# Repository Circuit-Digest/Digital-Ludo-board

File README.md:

# [Digital-Ludo-board](https://circuitdigest.com/microcontroller-projects/build-a-smart-digital-game-board-using-multicolour-pcb)

## Gallery

<table align="center">
  <tr>
    <td align="center">
      
    </td>
    <td align="center">
      
    </td>
  </tr>
  <tr>
    <td align="center">
      
    </td>
    <td align="center">
      
    </td>
  </tr>
</table>

---
Ludo, one of our cherished childhood board games, holds a special place in our hearts. Its simple yet engaging gameplay has provided countless hours of fun and bonding. However, as times have changed, so have our ways of enjoying these nostalgic pastimes. Today, children often experience classic games like Ludo through smartphones and gaming consoles, losing the physical gameplay and interpersonal connection of traditional board games.

What if we could bridge the gap between the old and the new by creating a digital version of the Ludo board? So let's create a Digital Ludo Board, a modern take on this classic game that combines the nostalgia of the physical game with the convenience and interactivity of the digital world. Designed and built from scratch, this is not only a fun project but also an opportunity to try out the new multicolor PCB.

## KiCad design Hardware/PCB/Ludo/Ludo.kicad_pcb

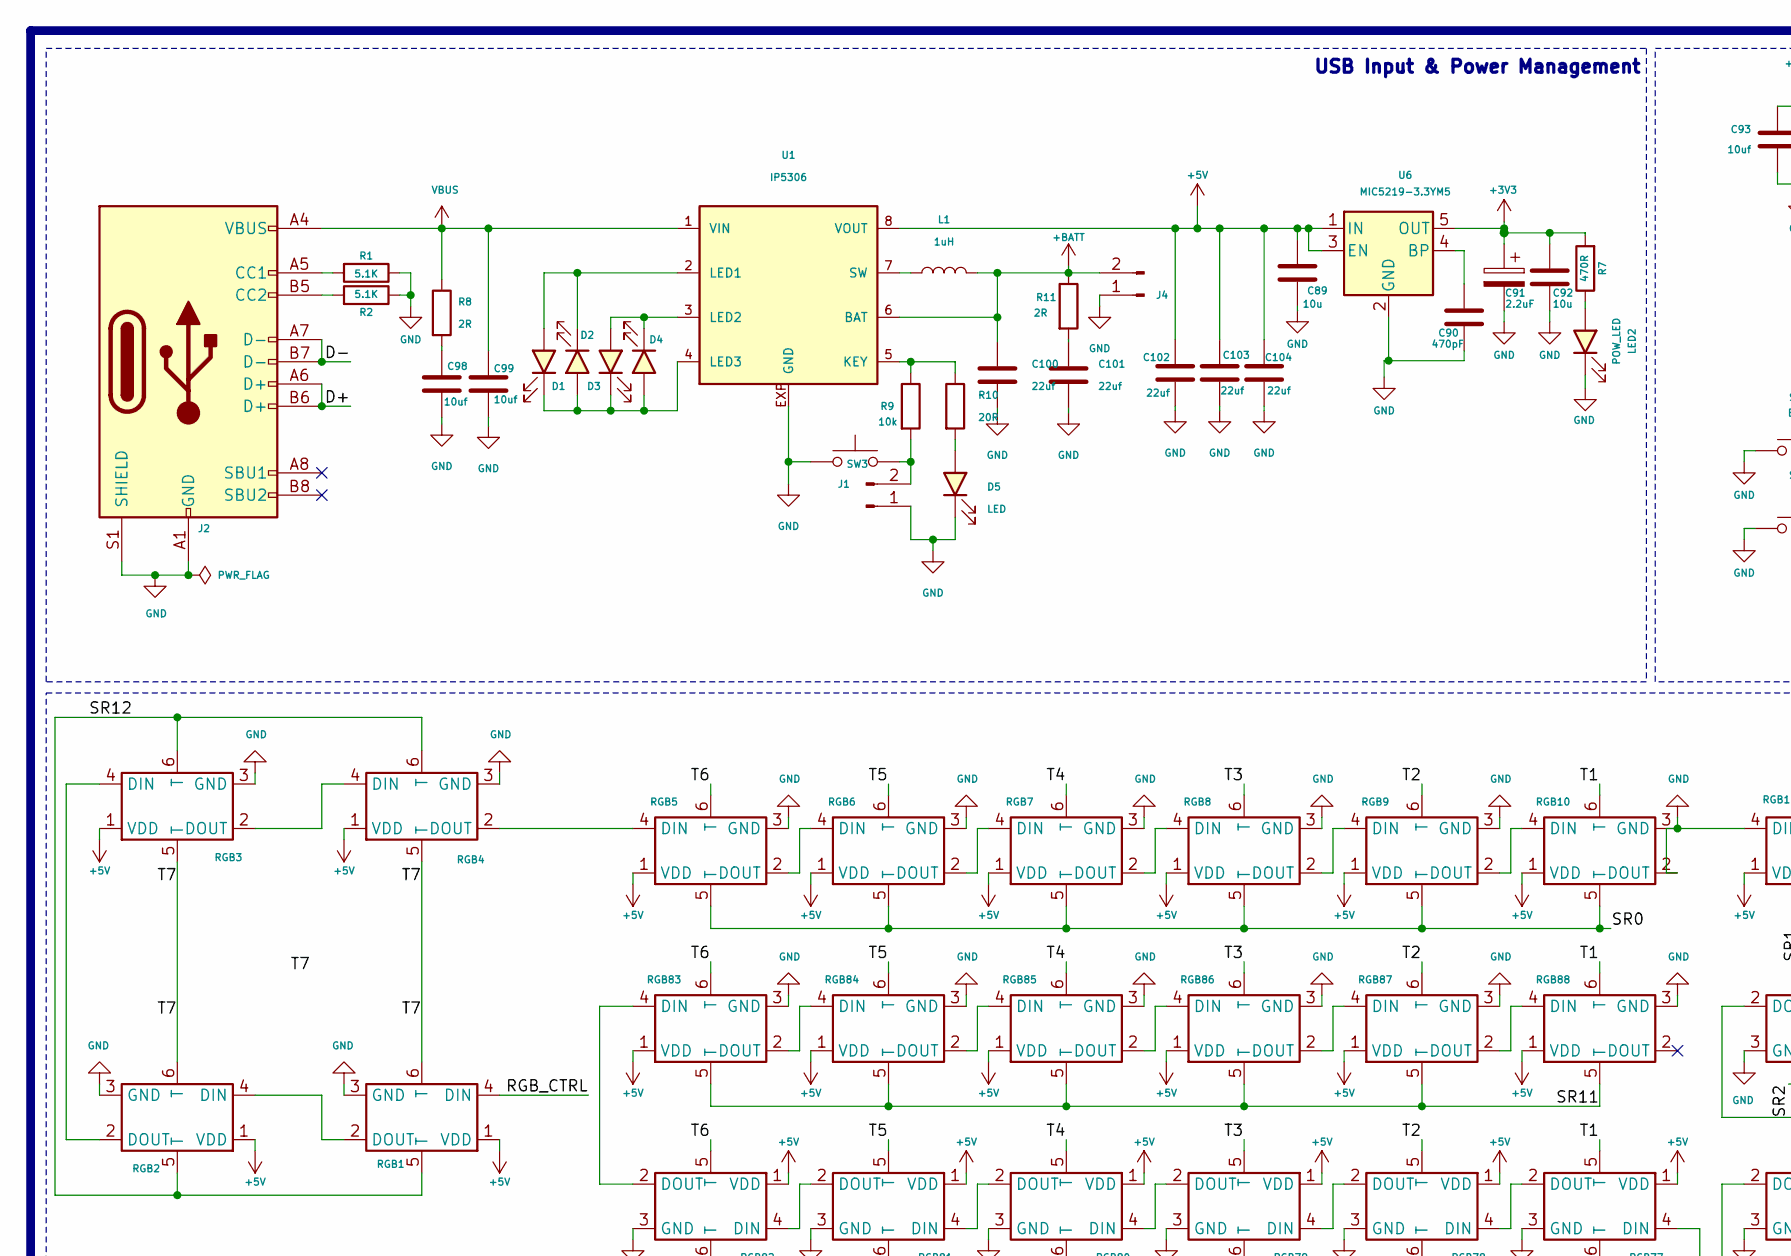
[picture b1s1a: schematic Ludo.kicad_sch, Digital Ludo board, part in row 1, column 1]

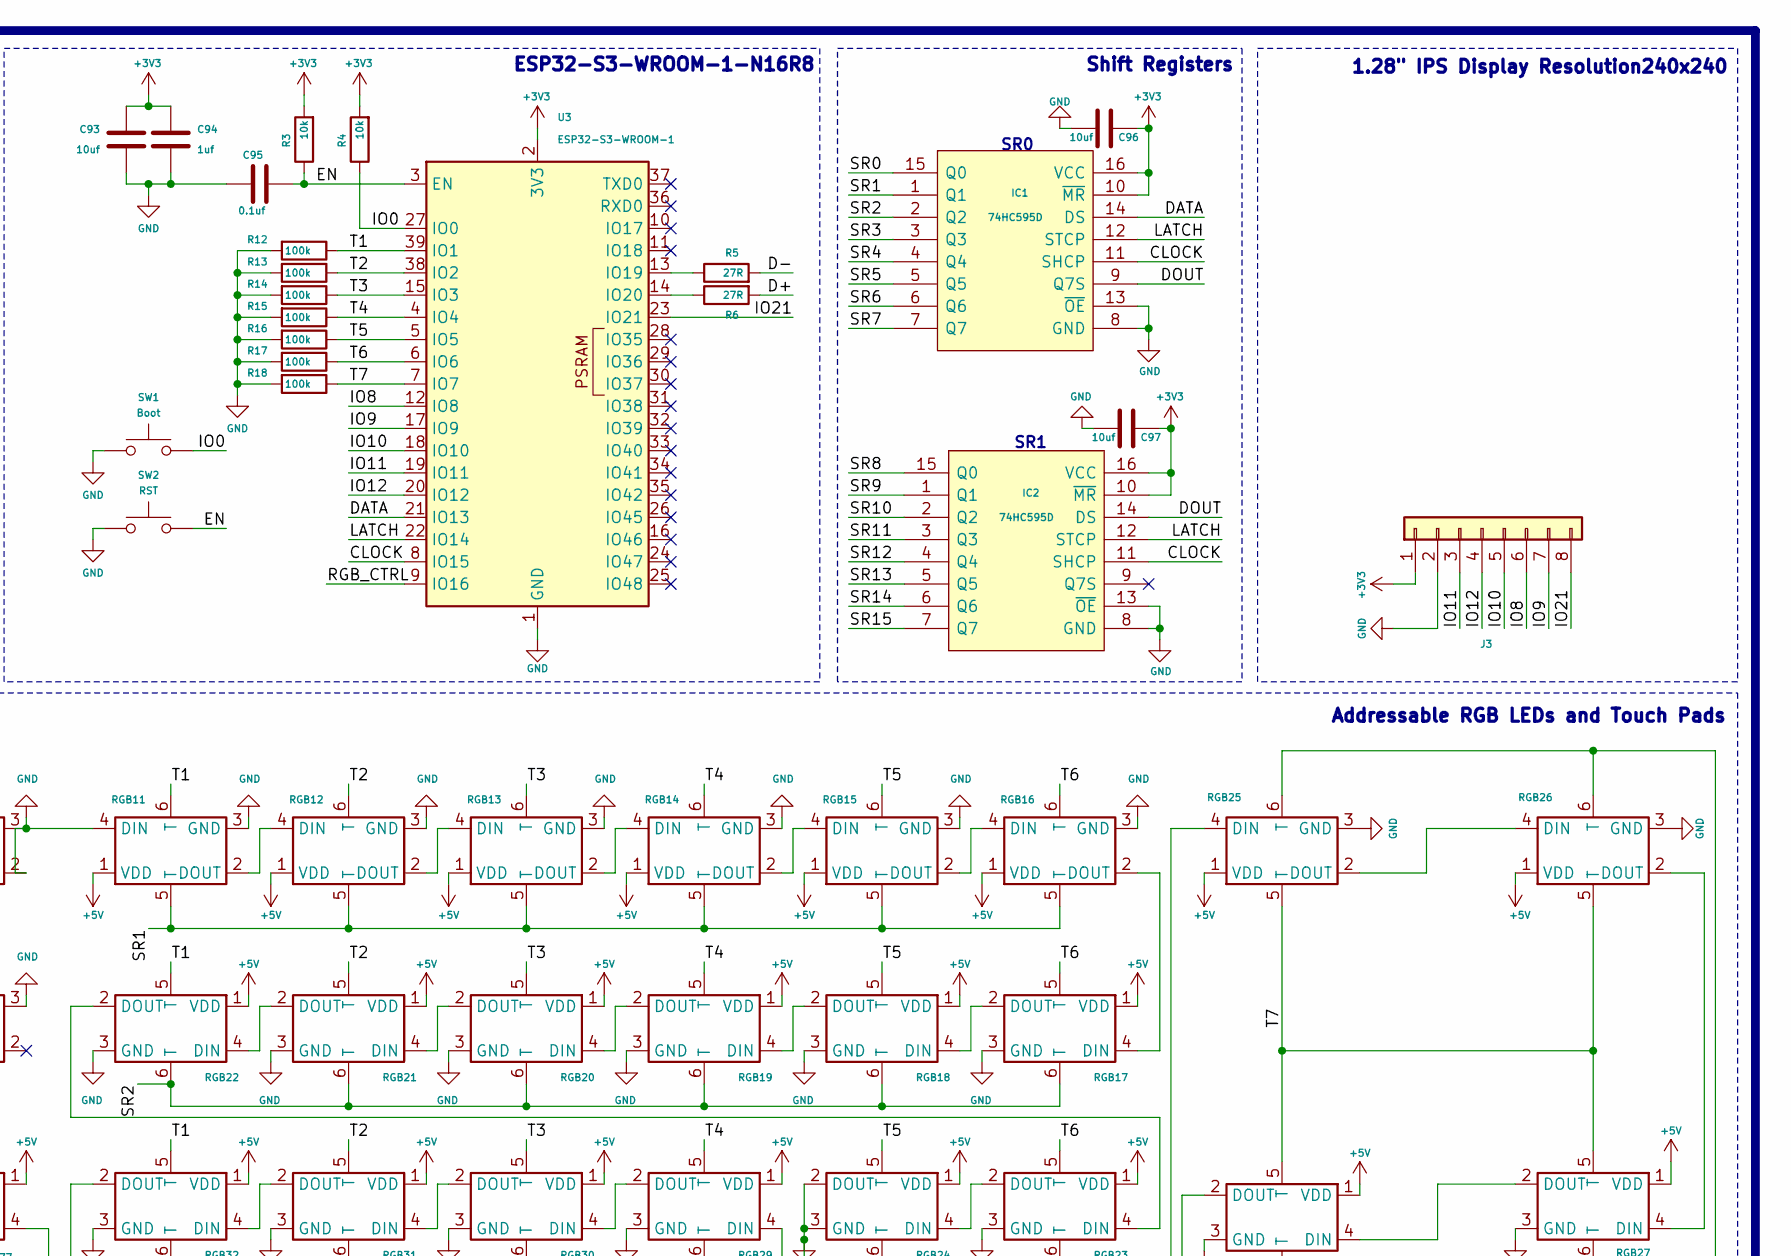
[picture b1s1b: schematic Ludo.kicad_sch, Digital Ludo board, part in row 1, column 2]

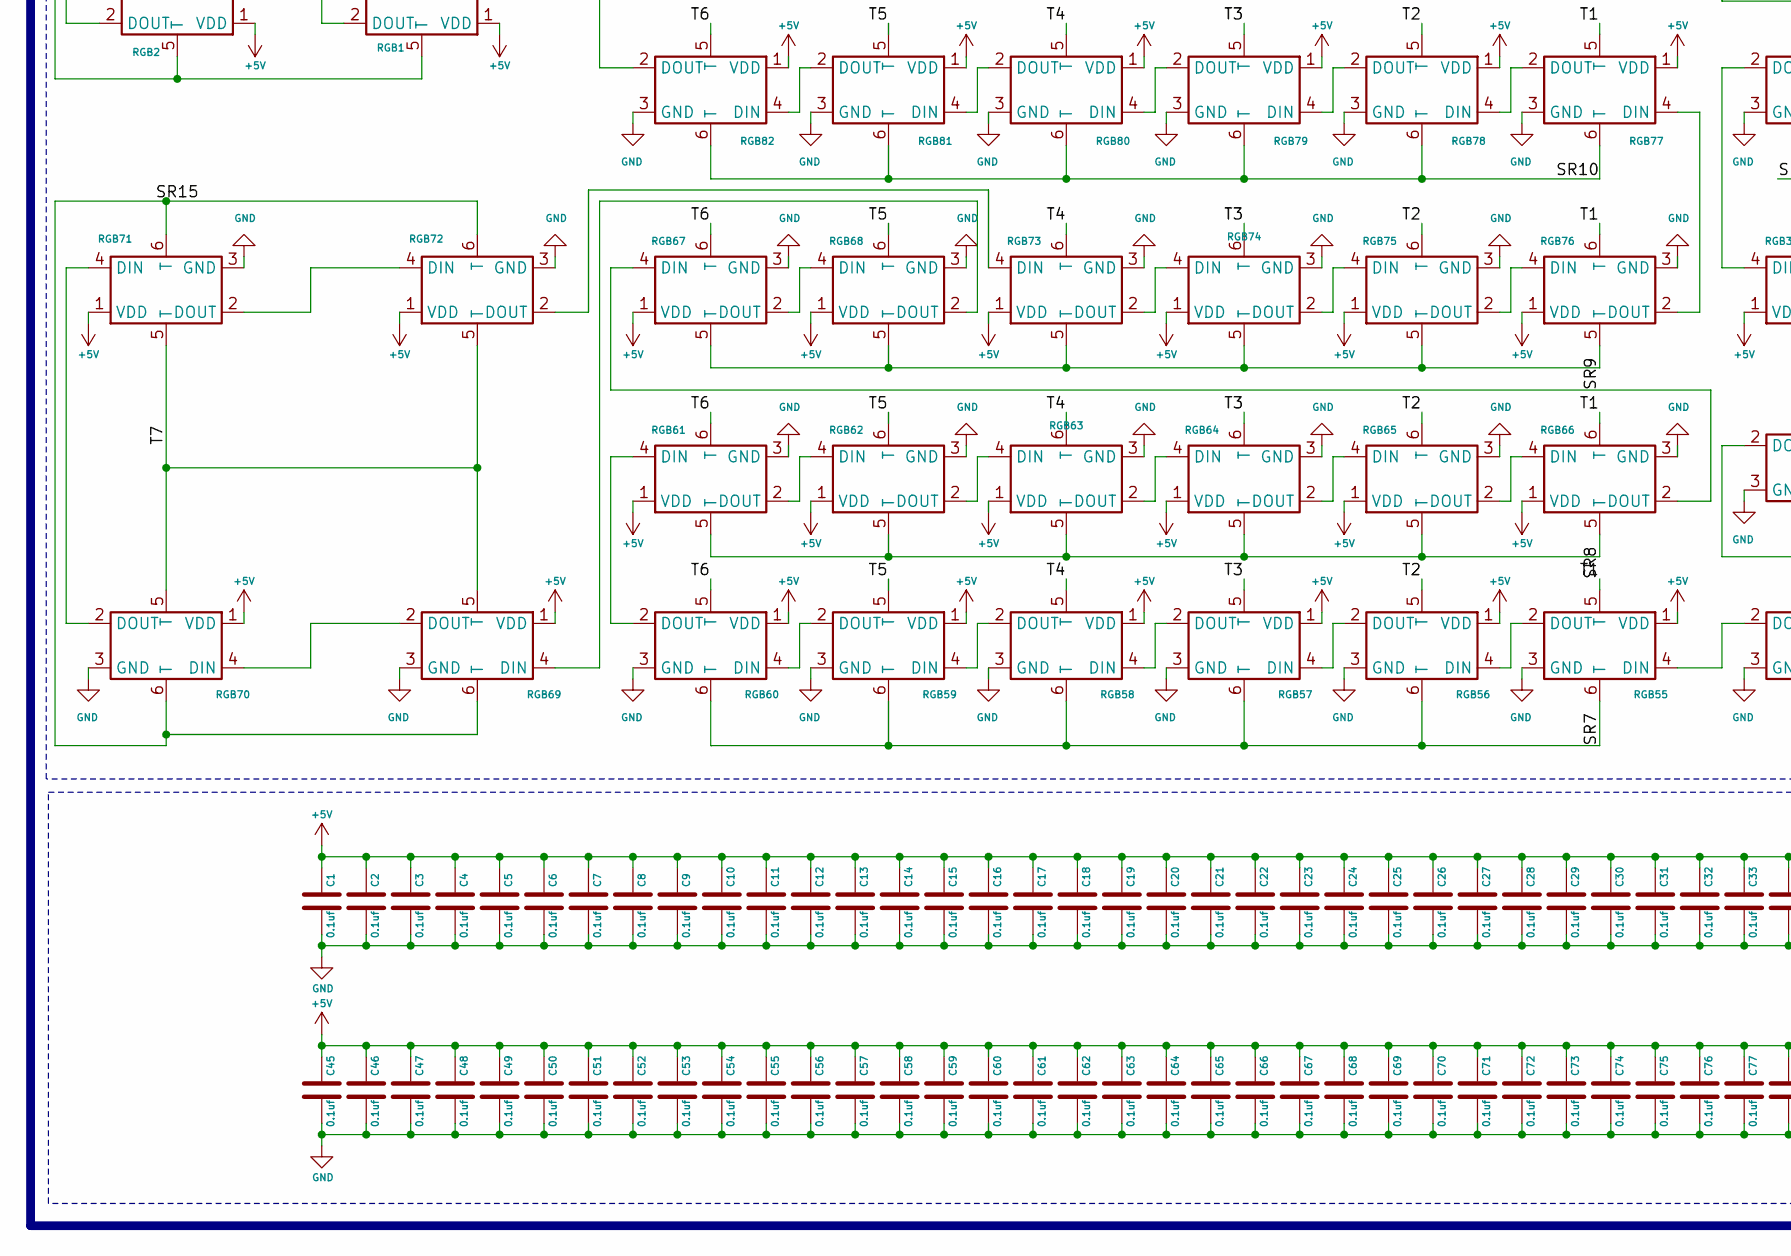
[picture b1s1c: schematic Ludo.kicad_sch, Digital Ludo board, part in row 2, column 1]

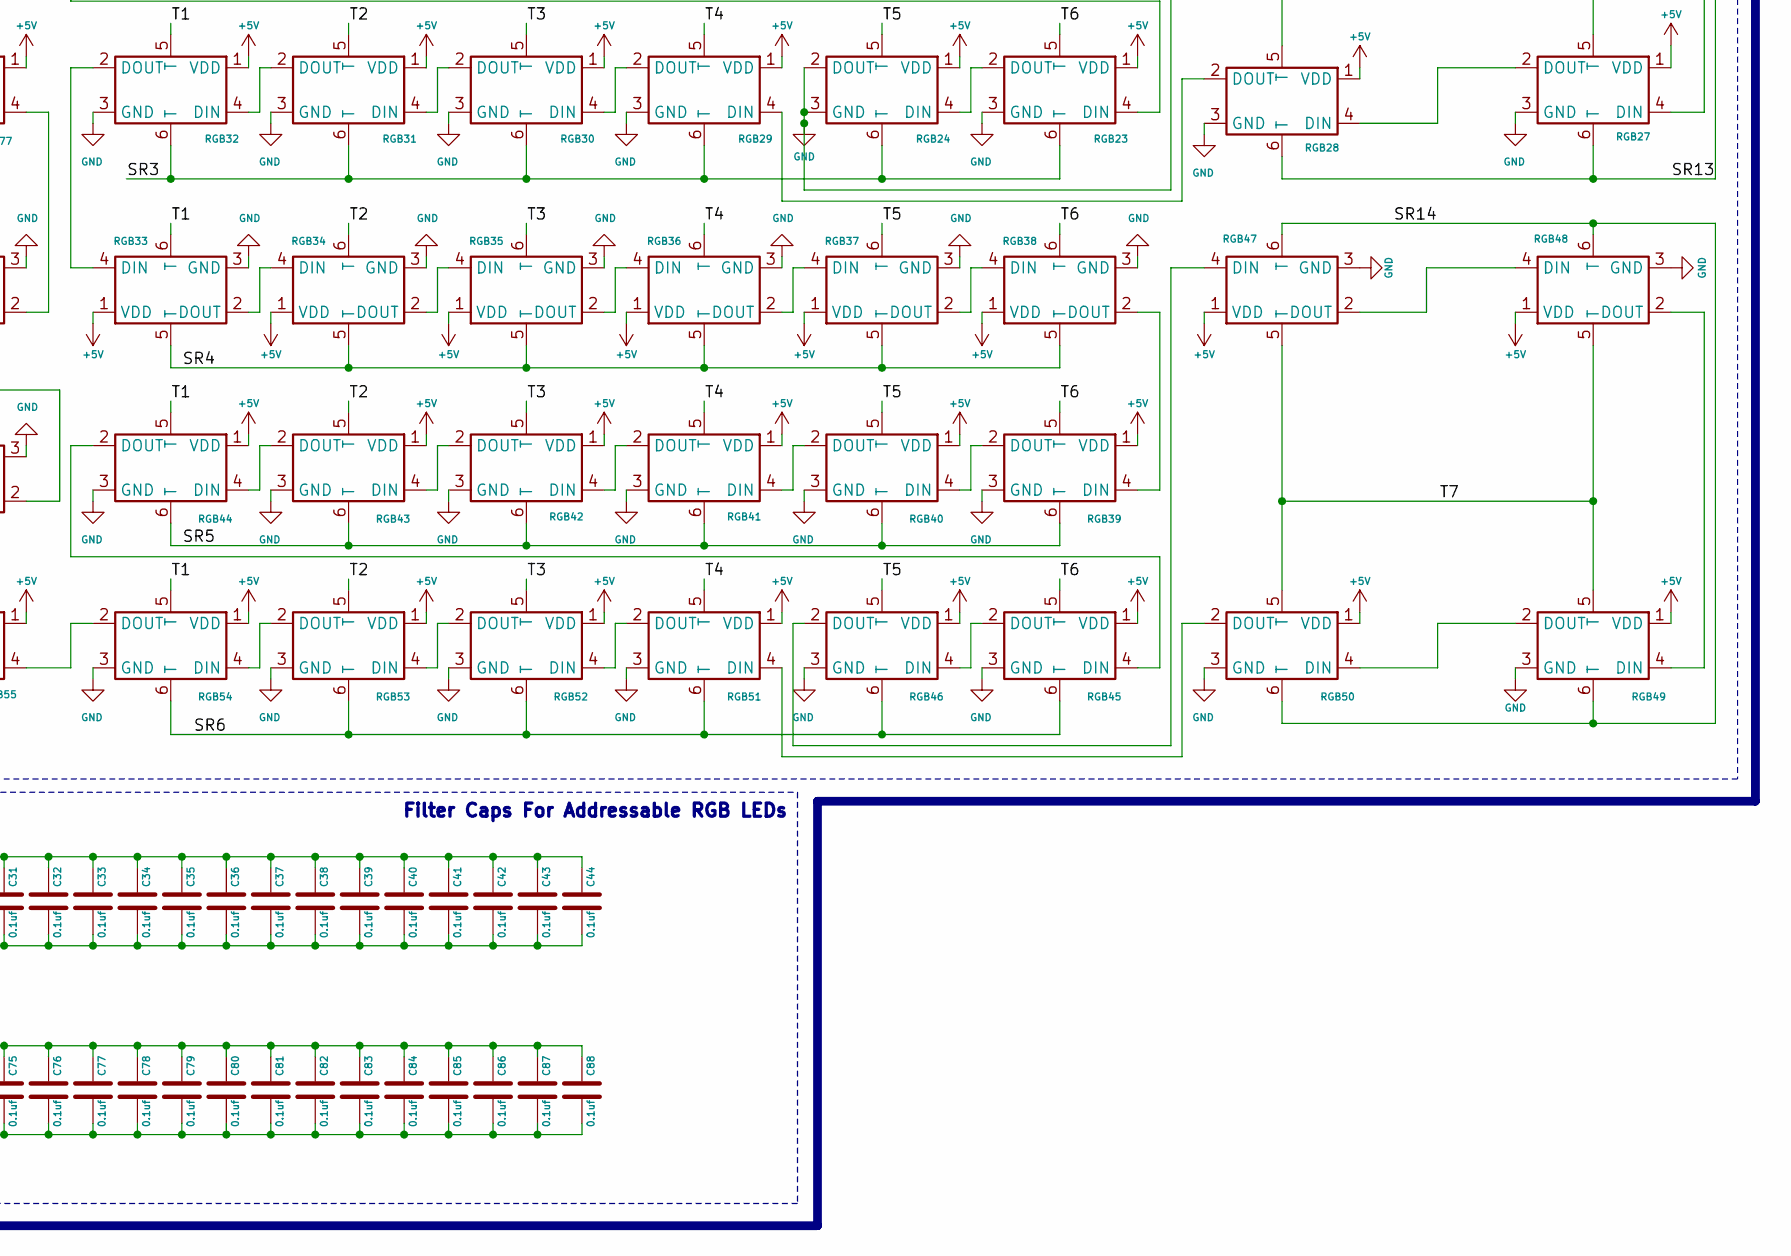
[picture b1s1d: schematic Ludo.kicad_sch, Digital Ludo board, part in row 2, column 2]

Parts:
C1, C2, C3, C4, C5, C6, C7, C8, C9, C10, C11, C12, C13, C14, C15, C16, C17, C18, C19, C20, C21, C22, C23, C24, C25, C26, C27, C28, C29, C30, C31, C32, C33, C34, C35, C36, C37, C38, C39, C40, C41, C42, C43, C44, C45, C46, C47, C48, C49, C50, C51, C52, C53, C54, C55, C56, C57, C58, C59, C60, C61, C62, C63, C64, C65, C66, C67, C68, C69, C70, C71, C72, C73, C74, C75, C76, C77, C78, C79, C80, C81, C82, C83, C84, C85, C86, C87, C88, C95: 0.1uf; C_0603_1608Metric
C89, C92: 10u; C_0603_1608Metric
C90: 470pF; C_0603_1608Metric
C91: 2.2uF; C_0805_2012Metric
C93, C96, C97, C98, C99: 10uf; C_0603_1608Metric
C94: 1uf; C_0603_1608Metric
C100, C101, C102, C103, C104: 22uf; C_0603_1608Metric
D1, D2, D3, D4, D5: LED; LED_0603_1608Metric
IC1, IC2: 74HC595D; 74HC595DQ100118; Mouser Part Number 771-74HC595D-Q100
J1, J4: Conn_01x02_Male; JST_PH_S2B-PH-SM4-TB_1x02-1MP_P2.00mm_Horizontal
J2: USB_C_Receptacle_USB2.0; USB_C_Receptacle_HRO_TYPE-C-31-M-12
J3: Conn_01x08; JST_PH_S8B-PH-SM4-TB_1x08-1MP_P2.00mm_Horizontal
L1: 1uH; IND1uh
LED2: POW_LED; LED_0603_1608Metric
R1, R2: 5.1K; R_0603_1608Metric
R3, R4, R9: 10k; R_0603_1608Metric
R5, R6: 27R; R_0603_1608Metric
R7: 470R; R_0603_1608Metric
R8, R11: 2R; R_0603_1608Metric
R10: 20R; R_0603_1608Metric
R12, R13, R14, R15, R16, R17, R18: 100k; R_0603_1608Metric
RGB1, RGB2, RGB3, RGB4, RGB5, RGB6, RGB7, RGB8, RGB9, RGB10, RGB11, RGB12, RGB13, RGB14, RGB15, RGB16, RGB17, RGB18, RGB19, RGB20, RGB21, RGB22, RGB23, RGB24, RGB25, RGB26, RGB27, RGB28, RGB29, RGB30, RGB31, RGB32, RGB33, RGB34, RGB35, RGB36, RGB37, RGB38, RGB39, RGB40, RGB41, RGB42, RGB43, RGB44, RGB45, RGB46, RGB47, RGB48, RGB49, RGB50, RGB51, RGB52, RGB53, RGB54, RGB55, RGB56, RGB57, RGB58, RGB59, RGB60, RGB61, RGB62, RGB63, RGB64, RGB65, RGB66, RGB67, RGB68, RGB69, RGB70, RGB71, RGB72, RGB73, RGB74, RGB75, RGB76, RGB77, RGB78, RGB79, RGB80, RGB81, RGB82, RGB83, RGB84, RGB85, RGB86, RGB87, RGB88: SK6812MINI-E_C5149201; SK6812MINI-E_1
SW1: Boot; Tactile 3x4x2mm TS-A010
SW2: RST; Tactile 3x4x2mm TS-A010
SW3: Boot; SW-SMD_TS24CA
U1: IP5306; IP5306-SOP8
U3: ESP32-S3-WROOM-1
U6: MIC5219-3.3YM5; SOT-23-5

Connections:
+3V3: C91.1, C92.1, C93.1, C94.1, C96.1, C97.1, IC1.10 (~MR), IC1.16 (VCC), IC2.10 (~MR), IC2.16 (VCC), J3.1, R3.2, R4.2, R7.2, U3.2 (3V3), U6.5 (OUT)
+5V: C1.1, C2.1, C3.1, C4.1, C5.1, C6.1, C7.1, C8.1, C9.1, C10.1, C11.1, C12.1, C13.1, C14.1, C15.1, C16.1, C17.1, C18.1, C19.1, C20.1, C21.1, C22.1, C23.1, C24.1, C25.1, C26.1, C27.1, C28.1, C29.1, C30.1, C31.1, C32.1, C33.1, C34.1, C35.1, C36.1, C37.1, C38.1, C39.1, C40.1, C41.1, C42.1, C43.1, C44.1, C45.1, C46.1, C47.1, C48.1, C49.1, C50.1, C51.1, C52.1, C53.1, C54.1, C55.1, C56.1, C57.1, C58.1, C59.1, C60.1, C61.1, C62.1, C63.1, C64.1, C65.1, C66.1, C67.1, C68.1, C69.1, C70.1, C71.1, C72.1, C73.1, C74.1, C75.1, C76.1, C77.1, C78.1, C79.1, C80.1, C81.1, C82.1, C83.1, C84.1, C85.1, C86.1, C87.1, C88.1, C89.1, C102.1, C103.1, C104.1, RGB1.1 (VDD), RGB2.1 (VDD), RGB3.1 (VDD), RGB4.1 (VDD), RGB5.1 (VDD), RGB6.1 (VDD), RGB7.1 (VDD), RGB8.1 (VDD), RGB9.1 (VDD), RGB10.1 (VDD), RGB11.1 (VDD), RGB12.1 (VDD), RGB13.1 (VDD), RGB14.1 (VDD), RGB15.1 (VDD), RGB16.1 (VDD), RGB17.1 (VDD), RGB18.1 (VDD), RGB19.1 (VDD), RGB20.1 (VDD), RGB21.1 (VDD), RGB22.1 (VDD), RGB23.1 (VDD), RGB24.1 (VDD), RGB25.1 (VDD), RGB26.1 (VDD), RGB27.1 (VDD), RGB28.1 (VDD), RGB29.1 (VDD), RGB30.1 (VDD), RGB31.1 (VDD), RGB32.1 (VDD), RGB33.1 (VDD), RGB34.1 (VDD), RGB35.1 (VDD), RGB36.1 (VDD), RGB37.1 (VDD), RGB38.1 (VDD), RGB39.1 (VDD), RGB40.1 (VDD), RGB41.1 (VDD), RGB42.1 (VDD), RGB43.1 (VDD), RGB44.1 (VDD), RGB45.1 (VDD), RGB46.1 (VDD), RGB47.1 (VDD), RGB48.1 (VDD), RGB49.1 (VDD), RGB50.1 (VDD), RGB51.1 (VDD), RGB52.1 (VDD), RGB53.1 (VDD), RGB54.1 (VDD), RGB55.1 (VDD), RGB56.1 (VDD), RGB57.1 (VDD), RGB58.1 (VDD), RGB59.1 (VDD), RGB60.1 (VDD), RGB61.1 (VDD), RGB62.1 (VDD), RGB63.1 (VDD), RGB64.1 (VDD), RGB65.1 (VDD), RGB66.1 (VDD), RGB67.1 (VDD), RGB68.1 (VDD), RGB69.1 (VDD), RGB70.1 (VDD), RGB71.1 (VDD), RGB72.1 (VDD), RGB73.1 (VDD), RGB74.1 (VDD), RGB75.1 (VDD), RGB76.1 (VDD), RGB77.1 (VDD), RGB78.1 (VDD), RGB79.1 (VDD), RGB80.1 (VDD), RGB81.1 (VDD), RGB82.1 (VDD), RGB83.1 (VDD), RGB84.1 (VDD), RGB85.1 (VDD), RGB86.1 (VDD), RGB87.1 (VDD), RGB88.1 (VDD), U1.8 (VOUT), U6.1 (IN), U6.3 (EN)
+BATT: C100.1, J4.2, L1.2, R11.1, U1.6 (BAT)
/CLOCK: IC1.11 (SHCP), IC2.11 (SHCP), U3.8 (IO15)
/D+: J2.A6 (D+), J2.B6 (D+), R6.2
/D-: J2.A7 (D-), J2.B7 (D-), R5.2
/DATA: IC1.14 (DS), U3.21 (IO13)
/DOUT: IC1.9 (Q7S), IC2.14 (DS)
/EN: C95.1, R3.1, SW2.2, U3.3 (EN)
/IO0: R4.1, SW1.2, U3.27 (IO0)
/IO8: J3.6, U3.12 (IO8)
/IO9: J3.7, U3.17 (IO9)
/IO10: J3.5, U3.18 (IO10)
/IO11: J3.3, U3.19 (IO11)
/IO12: J3.4, U3.20 (IO12)
/IO21: J3.8, U3.23 (IO21)
/LATCH: IC1.12 (STCP), IC2.12 (STCP), U3.22 (IO14)
/RGB_CTRL: RGB1.4 (DIN), U3.9 (IO16)
/SR0: IC1.15 (Q0), RGB5.5 (T), RGB6.5 (T), RGB7.5 (T), RGB8.5 (T), RGB9.5 (T), RGB10.5 (T)
/SR1: IC1.1 (Q1), RGB11.5 (T), RGB12.5 (T), RGB13.5 (T), RGB14.5 (T), RGB15.5 (T), RGB16.5 (T)
/SR2: IC1.2 (Q2), RGB17.6 (T), RGB18.6 (T), RGB19.6 (T), RGB20.6 (T), RGB21.6 (T), RGB22.6 (T)
/SR3: IC1.3 (Q3), RGB23.6 (T), RGB24.6 (T), RGB29.6 (T), RGB30.6 (T), RGB31.6 (T), RGB32.6 (T)
/SR4: IC1.4 (Q4), RGB33.5 (T), RGB34.5 (T), RGB35.5 (T), RGB36.5 (T), RGB37.5 (T), RGB38.5 (T)
/SR5: IC1.5 (Q5), RGB39.6 (T), RGB40.6 (T), RGB41.6 (T), RGB42.6 (T), RGB43.6 (T), RGB44.6 (T)
/SR6: IC1.6 (Q6), RGB45.6 (T), RGB46.6 (T), RGB51.6 (T), RGB52.6 (T), RGB53.6 (T), RGB54.6 (T)
/SR7: IC1.7 (Q7), RGB55.6 (T), RGB56.6 (T), RGB57.6 (T), RGB58.6 (T), RGB59.6 (T), RGB60.6 (T)
/SR8: IC2.15 (Q0), RGB61.5 (T), RGB62.5 (T), RGB63.5 (T), RGB64.5 (T), RGB65.5 (T), RGB66.5 (T)
/SR9: IC2.1 (Q1), RGB67.5 (T), RGB68.5 (T), RGB73.5 (T), RGB74.5 (T), RGB75.5 (T), RGB76.5 (T)
/SR10: IC2.2 (Q2), RGB77.6 (T), RGB78.6 (T), RGB79.6 (T), RGB80.6 (T), RGB81.6 (T), RGB82.6 (T)
/SR11: IC2.3 (Q3), RGB83.5 (T), RGB84.5 (T), RGB85.5 (T), RGB86.5 (T), RGB87.5 (T), RGB88.5 (T)
/SR12: IC2.4 (Q4), RGB1.5 (T), RGB2.5 (T), RGB3.6 (T), RGB4.6 (T)
/SR13: IC2.5 (Q5), RGB25.6 (T), RGB26.6 (T), RGB27.6 (T), RGB28.6 (T)
/SR14: IC2.6 (Q6), RGB47.6 (T), RGB48.6 (T), RGB49.6 (T), RGB50.6 (T)
/SR15: IC2.7 (Q7), RGB69.6 (T), RGB70.6 (T), RGB71.6 (T), RGB72.6 (T)
/T1: R12.1, RGB10.6 (T), RGB11.6 (T), RGB22.5 (T), RGB32.5 (T), RGB33.6 (T), RGB44.5 (T), RGB54.5 (T), RGB55.5 (T), RGB66.6 (T), RGB76.6 (T), RGB77.5 (T), RGB88.6 (T), U3.39 (IO1)
/T2: R13.1, RGB9.6 (T), RGB12.6 (T), RGB21.5 (T), RGB31.5 (T), RGB34.6 (T), RGB43.5 (T), RGB53.5 (T), RGB56.5 (T), RGB65.6 (T), RGB75.6 (T), RGB78.5 (T), RGB87.6 (T), U3.38 (IO2)
/T3: R14.1, RGB8.6 (T), RGB13.6 (T), RGB20.5 (T), RGB30.5 (T), RGB35.6 (T), RGB42.5 (T), RGB52.5 (T), RGB57.5 (T), RGB64.6 (T), RGB74.6 (T), RGB79.5 (T), RGB86.6 (T), U3.15 (IO3)
/T4: R15.1, RGB7.6 (T), RGB14.6 (T), RGB19.5 (T), RGB29.5 (T), RGB36.6 (T), RGB41.5 (T), RGB51.5 (T), RGB58.5 (T), RGB63.6 (T), RGB73.6 (T), RGB80.5 (T), RGB85.6 (T), U3.4 (IO4)
/T5: R16.1, RGB6.6 (T), RGB15.6 (T), RGB18.5 (T), RGB24.5 (T), RGB37.6 (T), RGB40.5 (T), RGB46.5 (T), RGB59.5 (T), RGB62.6 (T), RGB68.6 (T), RGB81.5 (T), RGB84.6 (T), U3.5 (IO5)
/T6: R17.1, RGB5.6 (T), RGB16.6 (T), RGB17.5 (T), RGB23.5 (T), RGB38.6 (T), RGB39.5 (T), RGB45.5 (T), RGB60.5 (T), RGB61.6 (T), RGB67.6 (T), RGB82.5 (T), RGB83.6 (T), U3.6 (IO6)
/T7: R18.1, RGB1.6 (T), RGB2.6 (T), RGB3.5 (T), RGB4.5 (T), RGB25.5 (T), RGB26.5 (T), RGB27.5 (T), RGB28.5 (T), RGB47.5 (T), RGB48.5 (T), RGB49.5 (T), RGB50.5 (T), RGB69.5 (T), RGB70.5 (T), RGB71.5 (T), RGB72.5 (T), U3.7 (IO7)
unnamed: C98.1, R8.2
unnamed: C101.1, R11.2
unnamed: D1.2 (A), D2.1 (K), U1.2 (LED1)
unnamed: D1.1 (K), D2.2 (A), D3.1 (K), D4.2 (A), U1.4 (LED3)
unnamed: D3.2 (A), D4.1 (K), U1.3 (LED2)
unnamed: D5.2 (A), R10.2
unnamed: J1.2, R9.2, SW3.2
unnamed: J2.A5 (CC1), R1.2
unnamed: J2.B5 (CC2), R2.2
unnamed: LED2.2 (A), R7.1
unnamed: RGB1.2 (DOUT), RGB2.4 (DIN)
unnamed: RGB2.2 (DOUT), RGB3.4 (DIN)
unnamed: RGB3.2 (DOUT), RGB4.4 (DIN)
unnamed: RGB4.2 (DOUT), RGB5.4 (DIN)
unnamed: RGB5.2 (DOUT), RGB6.4 (DIN)
unnamed: RGB6.2 (DOUT), RGB7.4 (DIN)
unnamed: RGB7.2 (DOUT), RGB8.4 (DIN)
unnamed: RGB8.2 (DOUT), RGB9.4 (DIN)
unnamed: RGB9.2 (DOUT), RGB10.4 (DIN)
unnamed: RGB11.2 (DOUT), RGB12.4 (DIN)
unnamed: RGB12.2 (DOUT), RGB13.4 (DIN)
unnamed: RGB13.2 (DOUT), RGB14.4 (DIN)
unnamed: RGB14.2 (DOUT), RGB15.4 (DIN)
unnamed: RGB15.2 (DOUT), RGB16.4 (DIN)
unnamed: RGB16.2 (DOUT), RGB17.4 (DIN)
unnamed: RGB17.2 (DOUT), RGB18.4 (DIN)
unnamed: RGB18.2 (DOUT), RGB19.4 (DIN)
unnamed: RGB19.2 (DOUT), RGB20.4 (DIN)
unnamed: RGB20.2 (DOUT), RGB21.4 (DIN)
unnamed: RGB21.2 (DOUT), RGB22.4 (DIN)
unnamed: RGB22.2 (DOUT), RGB23.4 (DIN)
unnamed: RGB23.2 (DOUT), RGB24.4 (DIN)
unnamed: RGB25.2 (DOUT), RGB26.4 (DIN)
unnamed: RGB26.2 (DOUT), RGB27.4 (DIN)
unnamed: RGB27.2 (DOUT), RGB28.4 (DIN)
unnamed: RGB28.2 (DOUT), RGB29.4 (DIN)
unnamed: RGB29.2 (DOUT), RGB30.4 (DIN)
unnamed: RGB30.2 (DOUT), RGB31.4 (DIN)
unnamed: RGB31.2 (DOUT), RGB32.4 (DIN)
unnamed: RGB32.2 (DOUT), RGB33.4 (DIN)
unnamed: RGB33.2 (DOUT), RGB34.4 (DIN)
unnamed: RGB34.2 (DOUT), RGB35.4 (DIN)
unnamed: RGB35.2 (DOUT), RGB36.4 (DIN)
unnamed: RGB36.2 (DOUT), RGB37.4 (DIN)
unnamed: RGB37.2 (DOUT), RGB38.4 (DIN)
unnamed: RGB38.2 (DOUT), RGB39.4 (DIN)
unnamed: RGB39.2 (DOUT), RGB40.4 (DIN)
unnamed: RGB40.2 (DOUT), RGB41.4 (DIN)
unnamed: RGB41.2 (DOUT), RGB42.4 (DIN)
unnamed: RGB42.2 (DOUT), RGB43.4 (DIN)
unnamed: RGB43.2 (DOUT), RGB44.4 (DIN)
unnamed: RGB44.2 (DOUT), RGB45.4 (DIN)
unnamed: RGB45.2 (DOUT), RGB46.4 (DIN)
unnamed: RGB46.2 (DOUT), RGB47.4 (DIN)
unnamed: RGB47.2 (DOUT), RGB48.4 (DIN)
unnamed: RGB48.2 (DOUT), RGB49.4 (DIN)
unnamed: RGB49.2 (DOUT), RGB50.4 (DIN)
unnamed: RGB50.2 (DOUT), RGB51.4 (DIN)
unnamed: RGB51.2 (DOUT), RGB52.4 (DIN)
unnamed: RGB52.2 (DOUT), RGB53.4 (DIN)
unnamed: RGB53.2 (DOUT), RGB54.4 (DIN)
unnamed: RGB54.2 (DOUT), RGB55.4 (DIN)
unnamed: RGB55.2 (DOUT), RGB56.4 (DIN)
unnamed: RGB56.2 (DOUT), RGB57.4 (DIN)
unnamed: RGB57.2 (DOUT), RGB58.4 (DIN)
unnamed: RGB58.2 (DOUT), RGB59.4 (DIN)
unnamed: RGB59.2 (DOUT), RGB60.4 (DIN)
unnamed: RGB60.2 (DOUT), RGB61.4 (DIN)
unnamed: RGB61.2 (DOUT), RGB62.4 (DIN)
unnamed: RGB62.2 (DOUT), RGB63.4 (DIN)
unnamed: RGB63.2 (DOUT), RGB64.4 (DIN)
unnamed: RGB64.2 (DOUT), RGB65.4 (DIN)
unnamed: RGB65.2 (DOUT), RGB66.4 (DIN)
unnamed: RGB66.2 (DOUT), RGB67.4 (DIN)
unnamed: RGB67.2 (DOUT), RGB68.4 (DIN)
unnamed: RGB68.2 (DOUT), RGB69.4 (DIN)
unnamed: RGB69.2 (DOUT), RGB70.4 (DIN)
unnamed: RGB70.2 (DOUT), RGB71.4 (DIN)
unnamed: RGB71.2 (DOUT), RGB72.4 (DIN)
unnamed: RGB72.2 (DOUT), RGB73.4 (DIN)
unnamed: RGB73.2 (DOUT), RGB74.4 (DIN)
unnamed: RGB74.2 (DOUT), RGB75.4 (DIN)
unnamed: RGB75.2 (DOUT), RGB76.4 (DIN)
unnamed: RGB76.2 (DOUT), RGB77.4 (DIN)
unnamed: RGB77.2 (DOUT), RGB78.4 (DIN)
unnamed: RGB78.2 (DOUT), RGB79.4 (DIN)
unnamed: RGB79.2 (DOUT), RGB80.4 (DIN)
unnamed: RGB80.2 (DOUT), RGB81.4 (DIN)
unnamed: RGB81.2 (DOUT), RGB82.4 (DIN)
unnamed: RGB82.2 (DOUT), RGB83.4 (DIN)
unnamed: RGB83.2 (DOUT), RGB84.4 (DIN)
unnamed: RGB84.2 (DOUT), RGB85.4 (DIN)
unnamed: RGB85.2 (DOUT), RGB86.4 (DIN)
unnamed: RGB86.2 (DOUT), RGB87.4 (DIN)
unnamed: RGB87.2 (DOUT), RGB88.4 (DIN)
unnamed: R9.1, R10.1, U1.5 (KEY)
unnamed: L1.1, U1.7 (SW)
unnamed: R5.1, U3.13 (IO19)
unnamed: R6.1, U3.14 (IO20)
unnamed: C90.1, U6.4 (BP)
VBUS: C99.1, J2.A4 (VBUS), J2.A9 (VBUS), J2.B4 (VBUS), J2.B9 (VBUS), R8.1, U1.1 (VIN)

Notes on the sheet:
Shift Registers
SR0
Filter Caps For Addressable RGB LEDs
Addressable RGB LEDs and Touch Pads
ESP32-S3-WROOM-1-N16R8
USB Input & Power Management
SR1
1.28" IPS Display Resolution240x240

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
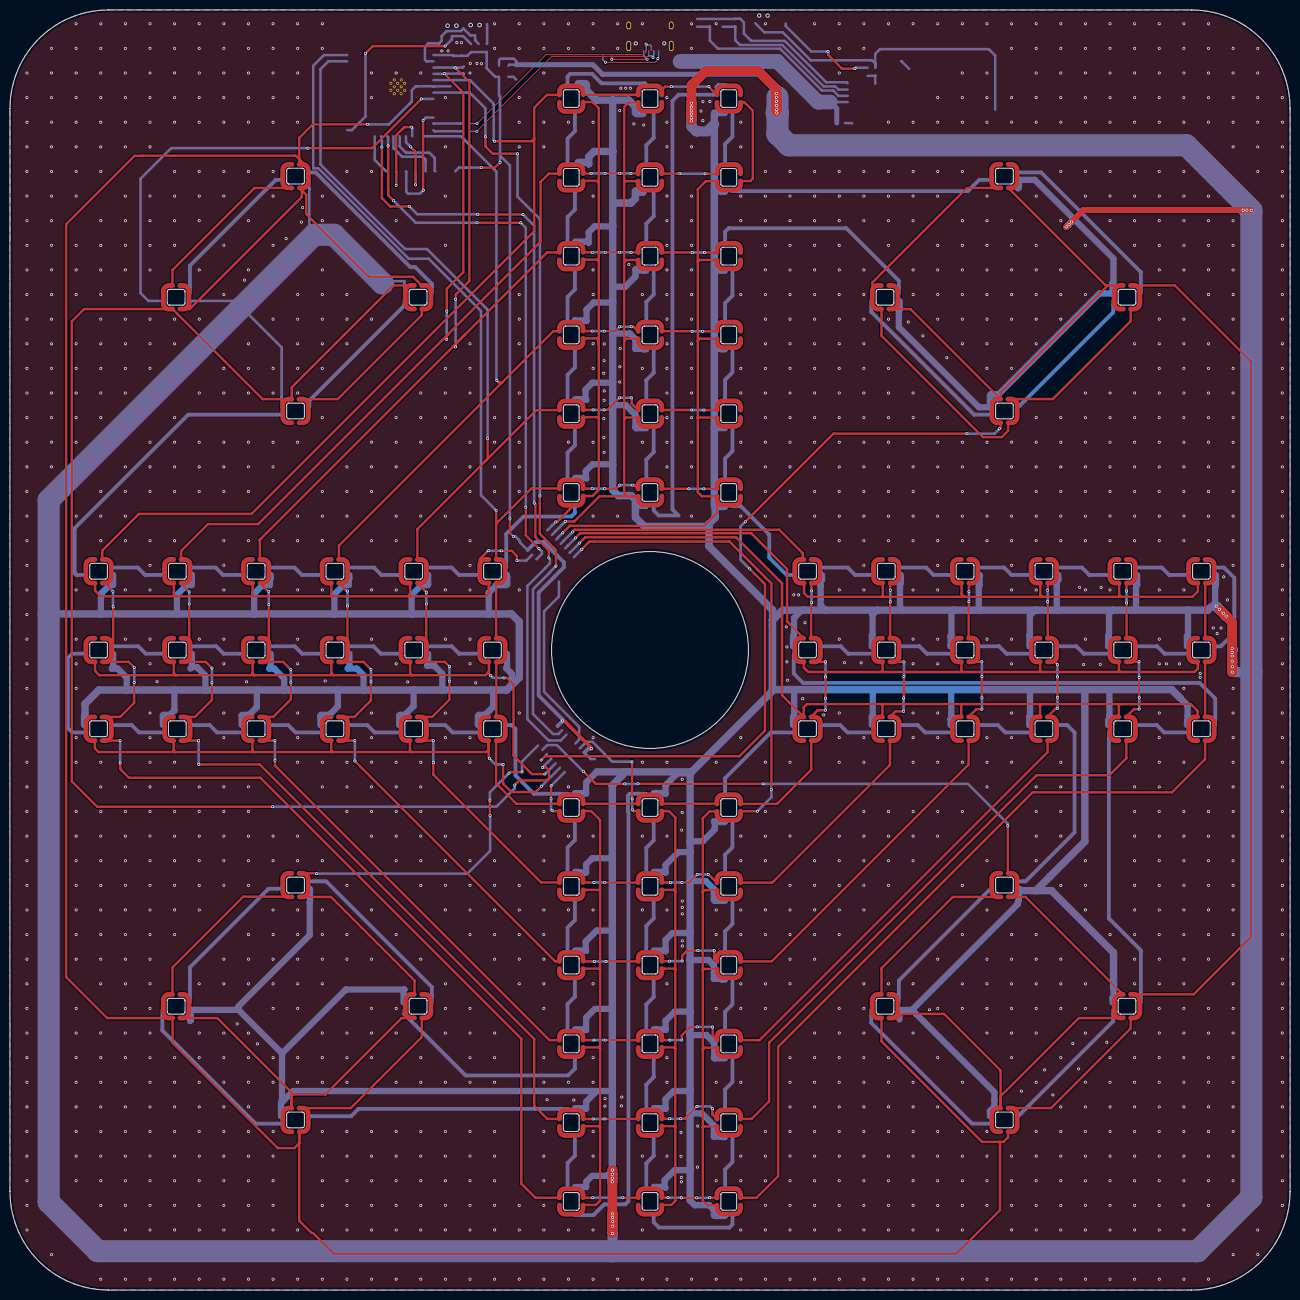
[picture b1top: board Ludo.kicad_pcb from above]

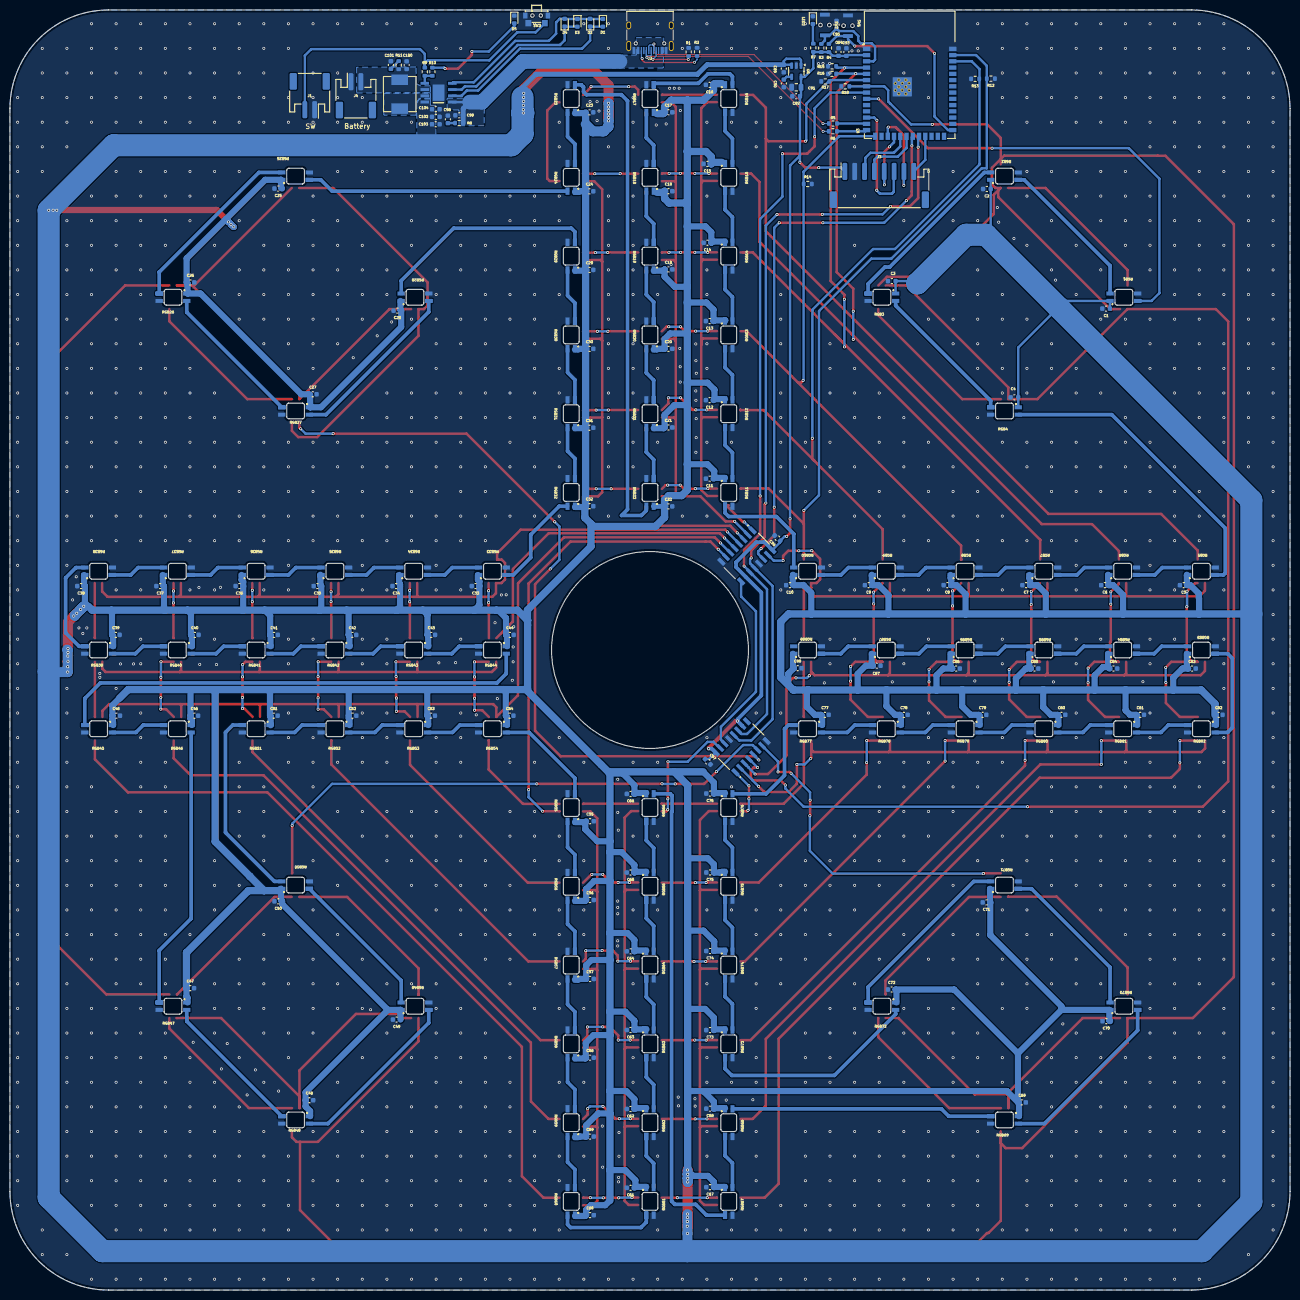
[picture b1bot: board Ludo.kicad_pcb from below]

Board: 2 copper layers, 260.0 x 260.0 mm, 229 parts (229 on the bottom side), 145 nets.

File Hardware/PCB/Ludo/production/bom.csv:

Designator,Footprint,Quantity,Value,LCSC Part #
"C1, C10, C11, C12, C13, C14, C15, C16, C17, C18, C19, C2, C20, C21, C22, C23, C24, C25, C26, C27, C28, C29, C3, C30, C31, C32, C33, C34, C35, C36, C37, C38, C39, C4, C40, C41, C42, C43, C44, C45, C46, C47, C48, C49, C5, C50, C51, C52, C53, C54, C55, C56, C57, C58, C59, C6, C60, C61, C62, C63, C64, C65, C66, C67, C68, C69, C7, C70, C71, C72, C73, C74, C75, C76, C77, C78, C79, C8, C80, C81, C82, C83, C84, C85, C86, C87, C88, C9",0603,88,0.1uf,
"C100, C101, C103, C104",0603,4,22uf,
C102,0603,1,22uf,
"C89, C92",0603,2,10u,
C90,0603,1,470pF,
C91,0805,1,2.2uF,
"C93, C96, C97, C98, C99",0603,5,10uf,
C94,0603,1,1uf,
C95,0603,1,0.1uf,
D1,0603,1,LED,
"D2, D3, D4, D5",0603,4,LED,
"IC1, IC2",74HC595DQ100118,2,74HC595D,
"J1, J4",JST_PH_S2B-PH-SM4-TB_1x02-1MP_P2.00mm_Horizontal,2,Conn_01x02_Male,
J2,USB_C_Receptacle_HRO_TYPE-C-31-M-12,1,USB_C_Receptacle_USB2.0,
J3,JST_PH_S8B-PH-SM4-TB_1x08-1MP_P2.00mm_Horizontal,1,Conn_01x08,
L1,IND1uh,1,1uH,
LED2,0603,1,POW_LED,
"R1, R2",0603,2,5.1K,
R10,0603,1,20R,
"R11, R8",0603,2,2R,
"R12, R13, R14, R15, R16, R17, R18",0603,7,100k,
"R3, R4, R9",0603,3,10k,
"R5, R6",0603,2,27R,
R7,0603,1,470R,
"RGB1, RGB10, RGB11, RGB12, RGB13, RGB14, RGB15, RGB16, RGB17, RGB18, RGB19, RGB2, RGB20, RGB21, RGB22, RGB23, RGB24, RGB25, RGB26, RGB27, RGB28, RGB29, RGB3, RGB30, RGB31, RGB32, RGB33, RGB34, RGB35, RGB36, RGB37, RGB38, RGB39, RGB4, RGB40, RGB41, RGB42, RGB43, RGB44, RGB45, RGB46, RGB47, RGB48, RGB49, RGB5, RGB50, RGB51, RGB52, RGB53, RGB54, RGB55, RGB56, RGB57, RGB58, RGB59, RGB6, RGB60, RGB61, RGB62, RGB63, RGB64, RGB65, RGB66, RGB67, RGB68, RGB69, RGB7, RGB70, RGB71, RGB72, RGB73, RGB74, RGB75, RGB76, RGB77, RGB78, RGB79, RGB8, RGB80, RGB81, RGB82, RGB83, RGB84, RGB85, RGB86, RGB87, RGB88, RGB9",SK6812MINI-E_1,88,SK6812MINI-E_C5149201,
SW1,Tactile 3x4x2mm TS-A010,1,Boot,
SW2,Tactile 3x4x2mm TS-A010,1,RST,
SW3,SW-SMD_TS24CA,1,Boot,
U1,IP5306-SOP8,1,IP5306,
U3,ESP32-S3-WROOM-1,1,ESP32-S3-WROOM-1,
U6,SOT-23-5,1,MIC5219-3.3YM5,
